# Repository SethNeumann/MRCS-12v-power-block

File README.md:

# MRCS-12v-power-block
## License: Creative Commons Attribution-NonCommercial-ShareAlike

Power distribution block for cTc controlled locked turnouts

Initial version based on Seth v20191115

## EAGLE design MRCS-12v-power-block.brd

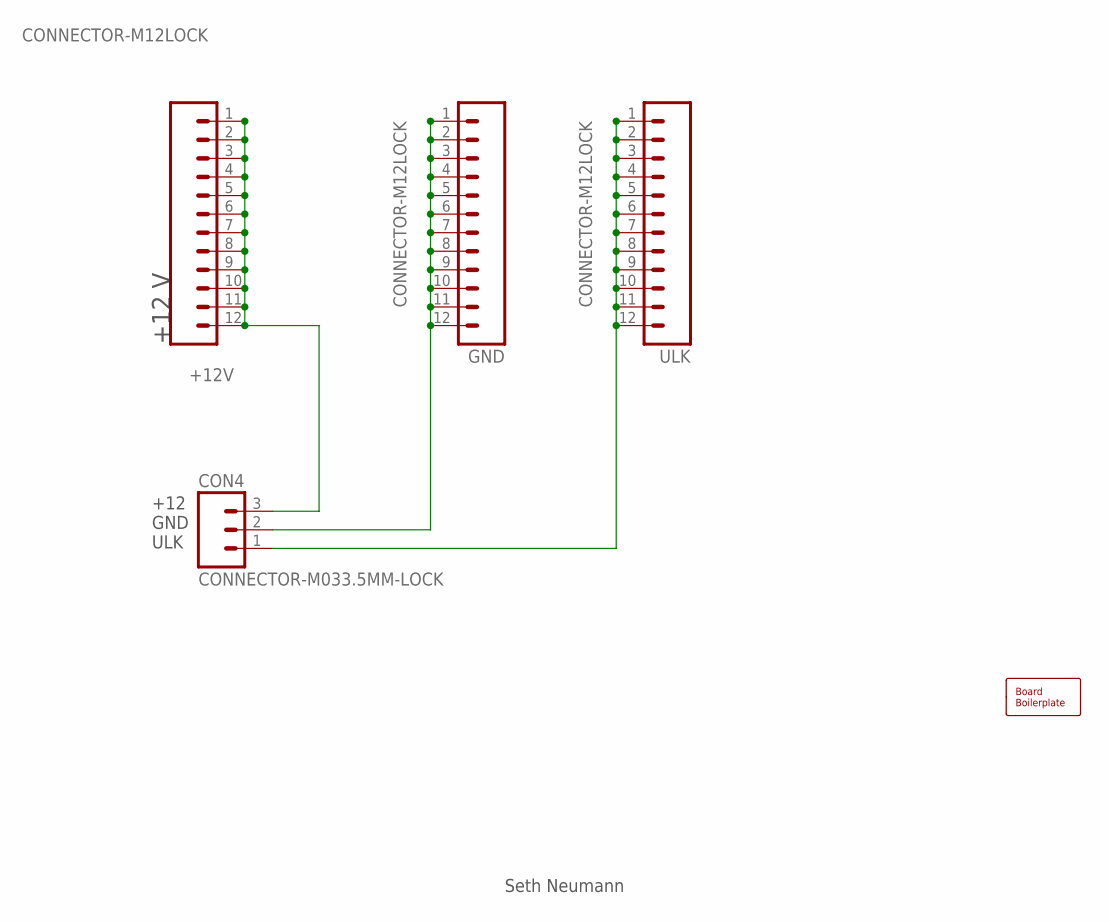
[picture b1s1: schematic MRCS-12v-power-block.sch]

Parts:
+12V: CONNECTOR-M12LOCK; 1X12_LOCK
BOARD1: BOARD50X50; BOARD-SEEED5X5
CON4: CONNECTOR-M033.5MM-LOCK; SCREWTERMINAL-3.5MM-3_LOCK.007S
GND: CONNECTOR-M12LOCK; 1X12_LOCK
ULK: CONNECTOR-M12LOCK; 1X12_LOCK

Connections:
unnamed: CON4.2, GND.1, GND.2, GND.3, GND.4, GND.5, GND.6, GND.7, GND.8, GND.9, GND.10, GND.11, GND.12
unnamed: CON4.1, ULK.1, ULK.2, ULK.3, ULK.4, ULK.5, ULK.6, ULK.7, ULK.8, ULK.9, ULK.10, ULK.11, ULK.12
unnamed: +12V.1, +12V.2, +12V.3, +12V.4, +12V.5, +12V.6, +12V.7, +12V.8, +12V.9, +12V.10, +12V.11, +12V.12, CON4.3

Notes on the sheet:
+12 V
+12 GND ULK
Seth Neumann

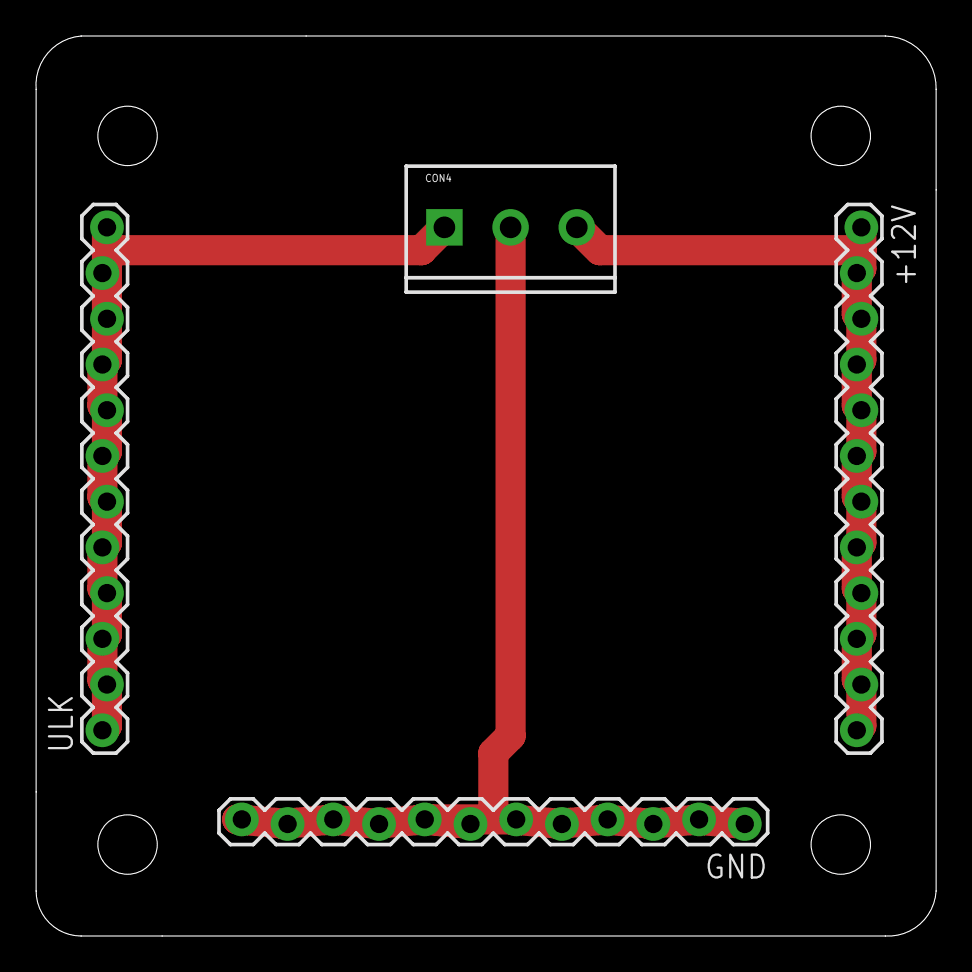
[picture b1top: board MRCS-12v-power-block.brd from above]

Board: 2 copper layers, 50.0 x 50.0 mm, 8 parts (0 on the bottom side), 3 nets.

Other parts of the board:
U$1: Prop65; CA-PROP65-BACK
U$2: MRCS; MRCSLOGOTOP
U$3: MRCS; MRCSLOGOBTM

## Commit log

2019-11-29 Initial version
2020-05-04 updated tags
2020-10-05 added missing values
